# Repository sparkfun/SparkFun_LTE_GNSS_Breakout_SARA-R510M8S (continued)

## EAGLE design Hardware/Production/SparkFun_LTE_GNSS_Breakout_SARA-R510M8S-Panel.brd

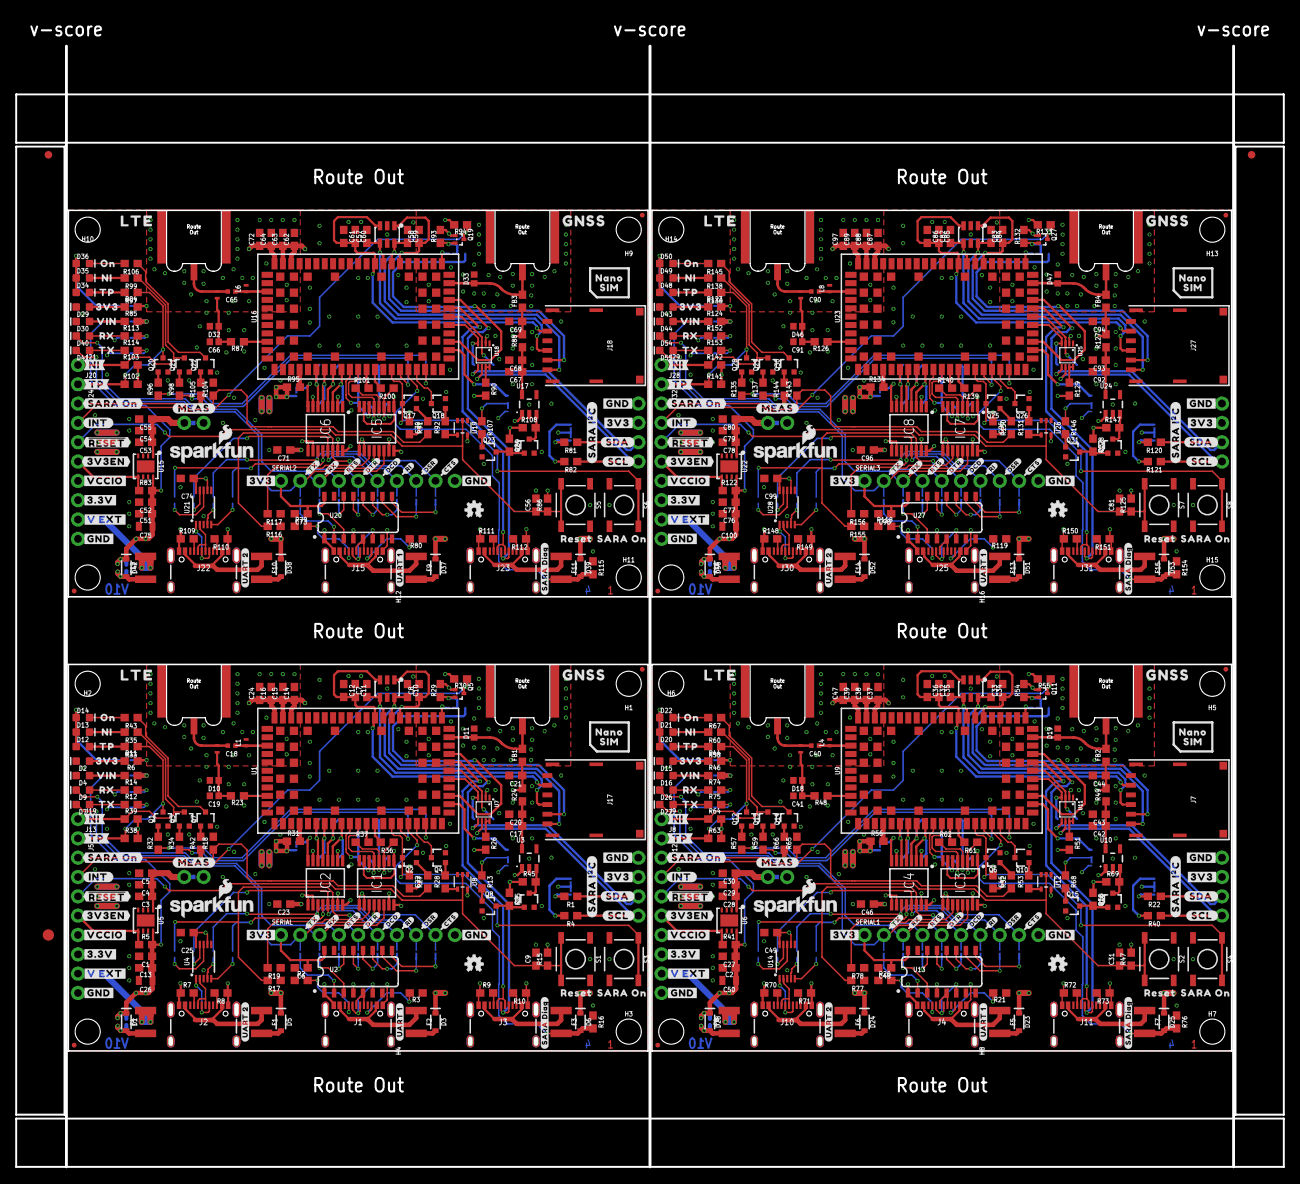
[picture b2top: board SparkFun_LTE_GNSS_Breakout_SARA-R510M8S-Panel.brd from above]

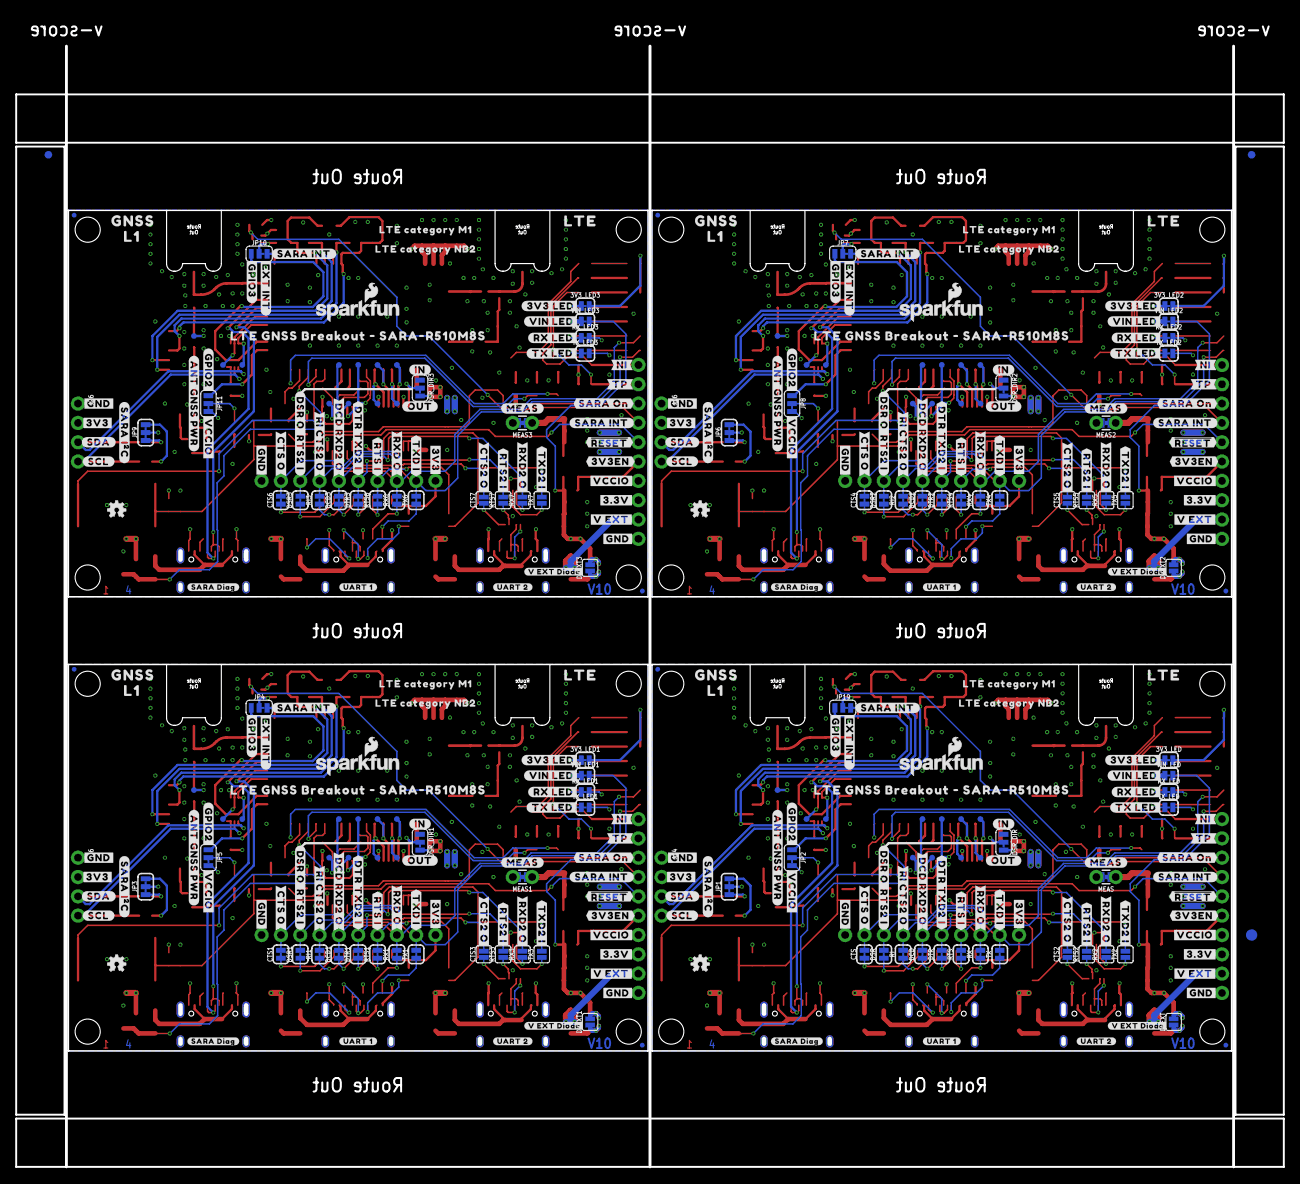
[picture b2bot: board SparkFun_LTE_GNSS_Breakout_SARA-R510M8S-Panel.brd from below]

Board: 4 copper layers, 166.6 x 147.3 mm, 1022 parts (363 on the bottom side), 444 nets.

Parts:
3V3_LED, 3V3_LED1, 3V3_LED2, 3V3_LED3: SMT-JUMPER_2_NC_TRACE_SILK
C1, C4, C6, C9, C12, C14, C20, C22, C23, C25, C27, C29, C31, C36, C37, C43, C45, C46, C48, C49, C52, C54, C56, C61, C62, C68, C70, C71, C73, C74, C77, C79, C81, C86, C87, C93, C95, C96, C98, C99: 0.1uF; 0603
C2, C5, C13, C30, C51, C55, C76, C80: 0.22uF; 0603
C3, C28, C53, C78: 4.7uF; 0603
C7, C8, C10, C11, C21, C32, C33, C34, C35, C44, C57, C58, C59, C60, C69, C82, C83, C84, C85, C94: 47pF; 0603
C15, C38, C63, C88: 68pF; 0603
C16, C39, C64, C89: 10uF; 0603
C17, C42, C67, C92: 1.0uF; 0603
C18, C40, C65, C90: 33pF; 0402-TIGHT
C19, C41, C66, C91: 27pF; 0402
C24, C47, C72, C97: 15pF; 0603
C26, C50, C75, C100: 10uF; 0805
CTS, CTS1, CTS4, CTS6: JUMPER-SMT_2_NC_TRACE_SILK; SMT-JUMPER_2_NC_TRACE_SILK
CTS2, CTS3, CTS5, CTS7: JUMPER-SMT_2_NO_SILK; SMT-JUMPER_2_NO_SILK
D1, D3, D5, D6, D23, D24, D25, D28, D37, D38, D39, D42, D51, D52, D53, D56: 3A/10V/280mV; SOD-323
D2, D15, D29, D43: RED; LED-0603
D4, D9, D16, D26, D30, D40, D44, D54: Yellow; LED-0603
D7, D12, D20, D27, D34, D41, D48, D55: GREEN; LED-0603
D8, D17, D31, D45: DT1042-04SO-7; SOT23-6L
D10, D11, D18, D19, D32, D33, D46, D47: PESD0402; 0402
D13, D21, D35, D49: BLUE; LED-0603
D14, D22, D36, D50: WHITE; LED-0603
DCD, DCD1, DCD2, DCD3: JUMPER-SMT_2_NC_TRACE_SILK; SMT-JUMPER_2_NC_TRACE_SILK
DSR, DSR1, DSR2, DSR3: JUMPER-SMT_2_NC_TRACE_SILK; SMT-JUMPER_2_NC_TRACE_SILK
DSR_DIR, DSR_DIR1, DSR_DIR2, DSR_DIR3: JUMPER-SMT_3_1-NC_TRACE_SILK; SMT-JUMPER_3_1-NC_TRACE_SILK
DTR, DTR1, DTR2, DTR3: JUMPER-SMT_2_NC_TRACE_SILK; SMT-JUMPER_2_NC_TRACE_SILK
DVEXT, DVEXT1, DVEXT2, DVEXT3: JUMPER-SMT_2_NO_SILK; SMT-JUMPER_2_NO_SILK
E1, E2, E3, E4, E5, E6, E7, E8: ANTENNA-SMA-GROUNDEDEDGE_SMA_SMD; SMA-EDGE-SMD
E$1, E$2, E$3, E$4: FIDUCIAL-1X2
E$5, E$6: FIDUCIAL-1.5X3
F1, F2, F3, F4, F5, F6, F7, F8, F9, F10, F11, F12, F13, F14, F15, F16: 6V/2A; 1210
FB1, FB2, FB3, FB4: 30Ω/1.8A; 0603
FD1, FD2, FD3, FD4, FD5, FD6, FD7, FD8, FD9, FD10, FD11, FD12, FD13, FD14, FD15, FD16: FIDUCIALUFIDUCIAL; FIDUCIAL-MICRO
H1, H2, H3, H4, H5, H6, H7, H8, H9, H10, H11, H12, H13, H14, H15, H16: STAND-OFF
IC1, IC2, IC3, IC4, IC5, IC6, IC7, IC8: SN74AVC4T774PW; SOP65P640X120-16N
J1, J2, J3, J4, J10, J11, J15, J22, J23, J25, J30, J31: USB-C-16P_4LAYER-PADS
J5, J12, J24, J32: 1X08_NO_SILK
J6, J14, J16, J26: 1X04_NO_SILK
J7, J17, J18, J27: NANO_SIM; NANO_SIM_WURTH_693043020611
J8, J13, J20, J28: TP; 1X01_NO_SILK
J9, J19, J21, J29: NI; 1X01_NO_SILK
JP1, JP3, JP6, JP9: SMT-JUMPER_3_2-NC_TRACE_SILK
JP2, JP4, JP5, JP7, JP8, JP10, JP11, JP19: JUMPER-SMT_3_1-NC_TRACE_SILK; SMT-JUMPER_3_1-NC_TRACE_SILK
L1, L4, L6, L8: DNP; 0402_COILCRAFT
L2, L3, L5, L7: 68nH; 0402_COILCRAFT
LOGO1, LOGO4, LOGO5, LOGO7, LOGO9, LOGO11, LOGO13, LOGO15: SFE_LOGO_NAME_FLAME.1_INCH; SFE_LOGO_NAME_FLAME_.1
LOGO2, LOGO3, LOGO6, LOGO8, LOGO10, LOGO12, LOGO14, LOGO16: OSHW-LOGOMINI; OSHW-LOGO-MINI
MEAS, MEAS1, MEAS2, MEAS3: COMBO-JUMPER_2_NC_TRACE
Q1, Q2, Q3, Q4, Q6, Q7, Q8, Q9, Q10, Q12, Q13, Q14, Q15, Q16, Q17, Q18, Q20, Q21, Q22, Q23, Q24, Q25, Q26, Q28, Q29, Q30, Q31, Q32: 310mA/60V/1.6Ω; SOT323
Q5, Q11, Q19, Q27: 20V/0.2A/8MHz/1.2Ω/1Vth; SOT-416FL
R1, R4, R22, R29, R30, R40, R54, R55, R81, R82, R93, R94, R120, R121, R132, R133: 2.2k; 0603
R2, R3, R7, R8, R9, R10, R16, R20, R21, R70, R71, R72, R73, R76, R79, R80, R109, R110, R111, R112, R115, R118, R119, R148, R149, R150, R151, R154: 5.1k; 0603
R5, R15, R17, R18, R19, R25, R38, R39, R41, R45, R47, R50, R63, R64, R65, R69, R77, R78, R83, R86, R89, R102, R103, R104, R108, R116, R117, R122, R125, R128, R141, R142, R143, R147, R155, R156: 100k; 0603
R6, R12, R14, R46, R74, R75, R85, R113, R114, R124, R152, R153: 4.7k; 0603
R11, R13, R27, R28, R32, R34, R42, R43, R44, R52, R53, R57, R59, R66, R67, R68, R84, R91, R92, R96, R98, R105, R106, R107, R123, R130, R131, R135, R137, R144, R145, R146: 1k; 0603
R23, R48, R87, R126: 10k; 0603
R24, R49, R88, R127: 10; 0603
R26, R51, R90, R129: 200k; 0603
R31, R36, R37, R56, R61, R62, R95, R100, R101, R134, R139, R140: 0; 0603
R33, R58, R97, R136: 100; 0603
R35, R60, R99, R138: 470; 0603
RI, RI1, RI2, RI3: JUMPER-SMT_2_NC_TRACE_SILK; SMT-JUMPER_2_NC_TRACE_SILK
RTS, RTS1, RTS4, RTS6: JUMPER-SMT_2_NC_TRACE_SILK; SMT-JUMPER_2_NC_TRACE_SILK
RTS2, RTS3, RTS5, RTS7: JUMPER-SMT_2_NO_SILK; SMT-JUMPER_2_NO_SILK
RX, RX1, RX4, RX6: JUMPER-SMT_2_NC_TRACE_SILK; SMT-JUMPER_2_NC_TRACE_SILK
RX2, RX3, RX5, RX7: JUMPER-SMT_2_NO_SILK; SMT-JUMPER_2_NO_SILK
RX_LED, RX_LED1, RX_LED2, RX_LED3: SMT-JUMPER_2_NC_TRACE_SILK
S1, S2, S5, S7: RESET; TACTILE_SWITCH_SMD_5.2MM
S3, S4, S6, S8: SARA_PWR; TACTILE_SWITCH_SMD_5.2MM
SERIAL, SERIAL1, SERIAL2, SERIAL3: 1X10_NO_SILK
TP1, TP2, TP3, TP4, TP5, TP6, TP7, TP8, TP9, TP10, TP11, TP12, TP13, TP14, TP15, TP16, TP17, TP18, TP19, TP20, TP21, TP22, TP23, TP24, TP25, TP26, TP27, TP28, TP29, TP30, TP31, TP32, TP33, TP34, TP35, TP36, TP37, TP38, TP39, TP40, TP41, TP42, TP43, TP44: TEST-POINT3; PAD.03X.03
TX, TX1, TX4, TX6: JUMPER-SMT_2_NC_TRACE_SILK; SMT-JUMPER_2_NC_TRACE_SILK
TX2, TX3, TX5, TX7: JUMPER-SMT_2_NO_SILK; SMT-JUMPER_2_NO_SILK
TX_LED, TX_LED1, TX_LED2, TX_LED3: SMT-JUMPER_2_NC_TRACE_SILK
U1, U9, U16, U23: SARA-R510M8S; SARA-LGA
U2, U13, U20, U27: CH340C; SO016
U3, U10, U17, U24: 3.3V; SOT23-5
U4, U14, U21, U28: CH340E_MSOP10; MSOP10
U5, U6, U15, U22: AP7361C-33FGE; UDFN-8
U7, U11, U18, U25: PCA9306; VSSOP_8PIN
U8, U12, U19, U26: 74HC1G04; SOT353
U$1, U$2, U$3, U$11, U$93, U$94, U$134, U$135, U$195, U$196, U$228, U$229, U$289, U$290, U$322, U$323: #3V3#1
U$4, U$167, U$261, U$355: #TX_LED#0
U$5, U$23, U$120, U$121, U$216, U$217, U$310, U$311: #SARA_I�C#0
U$6, U$7, U$136, U$137, U$230, U$231, U$324, U$325: #V_EXT#0
U$8, U$9, U$138, U$139, U$232, U$233, U$326, U$327: #3V3EN#0
U$10, U$13, U$140, U$141, U$234, U$235, U$328, U$329: ##RESET##0
U$12, U$22, U$95, U$96, U$197, U$198, U$291, U$292: #GND#0
U$14, U$142, U$236, U$330: #INT#0
U$15, U$71, U$182, U$183, U$276, U$277, U$370, U$371: #SARA_INT#0
U$16, U$17, U$143, U$144, U$237, U$238, U$331, U$332: #SARA_ON#0
U$18, U$145, U$239, U$333: RX0
U$19, U$87, U$92, U$115, U$194, U$213, U$288, U$307: #MEAS#2
U$20, U$168, U$262, U$356: #RX_LED#0
U$21, U$146, U$240, U$334: TX0
U$24, U$147, U$241, U$335: #TX#0
U$25, U$148, U$242, U$336: #RX#0
U$26, U$27, U$97, U$98, U$199, U$200, U$293, U$294: #SCL#3
U$28, U$149, U$243, U$337: #RTS#0
U$29, U$150, U$244, U$338: #DTR#0
U$30, U$37, U$102, U$103, U$201, U$202, U$295, U$296: #SDA#2
U$31, U$151, U$245, U$339: #DCD#0
U$32, U$152, U$246, U$340: #RI#0
U$33, U$153, U$247, U$341: #DSR#0
U$34, U$154, U$248, U$342: #CTS#0
U$35, U$155, U$249, U$343: #RXD_O#0
U$36, U$84, U$191, U$285: 3V37
U$38, U$156, U$250, U$344: #TXD_I#0
U$39, U$157, U$251, U$345: #CTS_O#0
U$40, U$158, U$252, U$346: #RTS_I#0
U$41, U$159, U$253, U$347: #DTR_TXD2_I#0
U$42, U$188, U$282, U$376: L10
U$43, U$160, U$254, U$348: #DCD_RXD2_O#0
U$44, U$161, U$255, U$349: #RXD2_O#0
U$45, U$85, U$192, U$286: RESET6
U$46, U$86, U$193, U$287: VIN8
U$47, U$162, U$256, U$350: #RI_CTS2_O#0
U$48, U$163, U$257, U$351: #CTS2_O#0
U$49, U$171, U$265, U$359: #DSR_O__RTS2_I#0
U$50, U$164, U$258, U$352: #RTS2_I#0
U$51, U$172, U$266, U$360: #V_EXT_DIODE#0
U$52, U$165, U$259, U$353: #OUT#0
U$53, U$166, U$260, U$354: #IN#0
U$54, U$169, U$263, U$357: #VIN_LED#0
U$55, U$56, U$77, U$78, U$81, U$82, U$104, U$105, U$189, U$190, U$203, U$204, U$283, U$284, U$297, U$298: #GND#4
U$57, U$58, U$106, U$107, U$205, U$206, U$299, U$300: #TP#0
U$59, U$60, U$108, U$109, U$207, U$208, U$301, U$302: #NI#0
U$61, U$170, U$264, U$358: #3V3_LED#0
U$62, U$63, U$173, U$174, U$267, U$268, U$361, U$362: #UART_2#0
U$64, U$65, U$175, U$176, U$269, U$270, U$363, U$364: #UART_1#0
U$66, U$67, U$177, U$178, U$271, U$272, U$365, U$366: #SARA_DIAG#0
U$68, U$80, U$83, U$112, U$114, U$179, U$211, U$212, U$273, U$305, U$306, U$367: #VCCIO#0
U$69, U$180, U$274, U$368: #GPIO2#0
U$70, U$181, U$275, U$369: #ANT_GNSS_PWR#0
U$72, U$187, U$281, U$375: #TXD2_I#0
U$73, U$184, U$278, U$372: LTE_CATEGORY_M10
U$74, U$185, U$279, U$373: LTE_CATEGORY_NB20
U$75, U$186, U$280, U$374: LTE_GNSS_BREAKOUT_#_SARA#R510M8S0
U$76, U$79, U$110, U$111, U$209, U$210, U$303, U$304: #3#3V#0
U$88, U$89, U$122, U$123, U$218, U$219, U$312, U$313: LTE0
U$90, U$116, U$214, U$308: NI0
U$91, U$117, U$215, U$309: TP0
U$99, U$100, U$124, U$125, U$220, U$221, U$314, U$315: GNSS0
U$101, U$127, U$223, U$317: ON0
U$113, U$126, U$222, U$316: SARA_ON0
U$118, U$132, U$226, U$320: #EXT_INT#0
U$119, U$133, U$227, U$321: #GPIO3#0
U$128, U$130, U$224, U$318: NANO0
U$129, U$131, U$225, U$319: SIM0
VIN_LED, VIN_LED1, VIN_LED2, VIN_LED3: SMT-JUMPER_2_NC_TRACE_SILK

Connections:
3.3V: 3V3_LED.2, C6.1, C14.1, C15.1, C16.1, C24.1, C25.1, D12.A, D13.A, D14.A, IC1.15, IC2.15, J5.6, J14.2, JP1.2, MEAS.2, MEAS.4, R15.2, R25.1, R26.2, R30.2, R38.2, R39.2, R45.1, RX_LED.2, SERIAL.1, TX_LED.2, U1.51, U1.52, U1.53, U2.4, U2.16, U4.7, U4.10, U8.5
3.3V1: 3V3_LED1.2, C37.1, C38.1, C39.1, C47.1, C48.1, C49.1, D20.A, D21.A, D22.A, IC3.15, IC4.15, J6.2, J12.6, JP3.2, MEAS1.2, MEAS1.4, R47.2, R50.1, R51.2, R55.2, R63.2, R64.2, R69.1, RX_LED1.2, SERIAL1.1, TX_LED1.2, U9.51, U9.52, U9.53, U12.5, U13.4, U13.16, U14.7, U14.10
3.3V2: 3V3_LED2.2, C62.1, C63.1, C64.1, C72.1, C73.1, C74.1, D34.A, D35.A, D36.A, IC5.15, IC6.15, J16.2, J24.6, JP6.2, MEAS2.2, MEAS2.4, R86.2, R89.1, R90.2, R94.2, R102.2, R103.2, R108.1, RX_LED2.2, SERIAL2.1, TX_LED2.2, U16.51, U16.52, U16.53, U19.5, U20.4, U20.16, U21.7, U21.10
3.3V3: 3V3_LED3.2, C87.1, C88.1, C89.1, C97.1, C98.1, C99.1, D48.A, D49.A, D50.A, IC7.15, IC8.15, J26.2, J32.6, JP9.2, MEAS3.2, MEAS3.4, R125.2, R128.1, R129.2, R133.2, R141.2, R142.2, R147.1, RX_LED3.2, SERIAL3.1, TX_LED3.2, U23.51, U23.52, U23.53, U26.5, U27.4, U27.16, U28.7, U28.10
3.3V_EN: J5.4, R5.1, U5.5
3.3V_EN1: J12.4, R41.1, U6.5
3.3V_EN2: J24.4, R83.1, U15.5
3.3V_EN3: J32.4, R122.1, U22.5
!RESET!: C9.1, J5.3, R15.1, S1.3, S1.4, U8.2
!RESET!1: C31.1, J12.3, R47.1, S2.3, S2.4, U12.2
!RESET!2: C56.1, J24.3, R86.1, S5.3, S5.4, U19.2
!RESET!3: C81.1, J32.3, R125.1, S7.3, S7.4, U26.2
ANT_REG_EN: Q9.3, R45.2, U3.3
ANT_REG_EN1: Q16.3, R69.2, U10.3
ANT_REG_EN2: Q24.3, R108.2, U17.3
ANT_REG_EN3: Q32.3, R147.2, U24.3
CTS: CTS.2, IC1.12, SERIAL.9
CTS1: CTS1.2, IC3.12, SERIAL1.9
CTS2: CTS4.2, IC5.12, SERIAL2.9
CTS3: CTS6.2, IC7.12, SERIAL3.9
DCD: DCD.2, IC2.13, RX2.2, SERIAL.6
DCD1: DCD1.2, IC4.13, RX3.2, SERIAL1.6
DCD2: DCD2.2, IC6.13, RX5.2, SERIAL2.6
DCD3: DCD3.2, IC8.13, RX7.2, SERIAL3.6
DSR: DSR.2, IC2.11, RTS2.2, SERIAL.8
DSR1: DSR1.2, IC4.11, RTS3.2, SERIAL1.8
DSR2: DSR2.2, IC6.11, RTS5.2, SERIAL2.8
DSR3: DSR3.2, IC8.11, RTS7.2, SERIAL3.8
DTR: DTR.2, IC2.14, R17.2, SERIAL.5, TX2.2
DTR1: DTR1.2, IC4.14, R77.2, SERIAL1.5, TX3.2
DTR2: DTR2.2, IC6.14, R116.2, SERIAL2.5, TX5.2
DTR3: DTR3.2, IC8.14, R155.2, SERIAL3.5, TX7.2
GND: C1.2, C3.2, C4.2, C5.2, C6.2, C7.2, C8.2, C9.2, C10.1, C11.1, C12.1, C13.2, C14.2, C15.2, C16.2, C17.2, C19.2, C20.2, C21.2, C22.2, C23.2, C24.2, C25.2, C26.2, D2.C, D4.C, D8.2, D8.5, D10.2, D11.2, DSR_DIR.1, E3.GND@0, E3.GND@1, E4.GND@0, E4.GND@1, IC1.2, IC1.8, IC1.9, IC1.10, IC2.1, IC2.9, IC2.10, J1.GND, J1.GND2, J2.GND, J2.GND2, J3.GND, J3.GND2, J5.8, J14.1, J17.C5, L1.P$2, Q1.2, Q2.2, Q3.2, Q4.2, Q7.2, Q8.2, Q9.2, R2.1, R3.1, R7.1, R8.1, R9.1, R10.1, R16.1, R17.1, R18.2, R19.1, S1.1, S1.2, S3.3, S3.4, SERIAL.10, U1.1, U1.3, U1.5, U1.14, U1.20, U1.21, U1.22, U1.30, U1.32, U1.43, U1.50, U1.54, U1.55, U1.57, U1.58, U1.59, U1.60, U1.61, U1.63, U1.64, U1.65, U1.66, U1.67, U1.68, U1.69, U1.70, U1.71, U1.72, U1.73, U1.74, U1.75, U1.76, U1.77, U1.78, U1.79, U1.80, U1.81, U1.82, U1.83, U1.84, U1.85, U1.86, U1.87, U1.88, U1.89, U1.90, U1.91, U1.92, U1.93, U1.94, U1.95, U1.96, U2.1, U3.2, U4.3, U5.4, U5.EP, U7.P1, U8.3
GND1: C2.2, C27.2, C28.2, C29.2, C30.2, C31.2, C32.2, C33.2, C34.1, C35.1, C36.1, C37.2, C38.2, C39.2, C41.2, C42.2, C43.2, C44.2, C45.2, C46.2, C47.2, C48.2, C49.2, C50.2, D15.C, D16.C, D17.2, D17.5, D18.2, D19.2, DSR_DIR1.1, E1.GND@0, E1.GND@1, E2.GND@0, E2.GND@1, IC3.2, IC3.8, IC3.9, IC3.10, IC4.1, IC4.9, IC4.10, J4.GND, J4.GND2, J6.1, J7.C5, J10.GND, J10.GND2, J11.GND, J11.GND2, J12.8, L4.P$2, Q6.2, Q10.2, Q12.2, Q13.2, Q14.2, Q15.2, Q16.2, R20.1, R21.1, R65.2, R70.1, R71.1, R72.1, R73.1, R76.1, R77.1, R78.1, S2.1, S2.2, S4.3, S4.4, SERIAL1.10, U6.4, U6.EP, U9.1, U9.3, U9.5, U9.14, U9.20, U9.21, U9.22, U9.30, U9.32, U9.43, U9.50, U9.54, U9.55, U9.57, U9.58, U9.59, U9.60, U9.61, U9.63, U9.64, U9.65, U9.66, U9.67, U9.68, U9.69, U9.70, U9.71, U9.72, U9.73, U9.74, U9.75, U9.76, U9.77, U9.78, U9.79, U9.80, U9.81, U9.82, U9.83, U9.84, U9.85, U9.86, U9.87, U9.88, U9.89, U9.90, U9.91, U9.92, U9.93, U9.94, U9.95, U9.96, U10.2, U11.P1, U12.3, U13.1, U14.3
GND2: C51.2, C52.2, C53.2, C54.2, C55.2, C56.2, C57.2, C58.2, C59.1, C60.1, C61.1, C62.2, C63.2, C64.2, C66.2, C67.2, C68.2, C69.2, C70.2, C71.2, C72.2, C73.2, C74.2, C75.2, D29.C, D30.C, D31.2, D31.5, D32.2, D33.2, DSR_DIR2.1, E5.GND@0, E5.GND@1, E6.GND@0, E6.GND@1, IC5.2, IC5.8, IC5.9, IC5.10, IC6.1, IC6.9, IC6.10, J15.GND, J15.GND2, J16.1, J18.C5, J22.GND, J22.GND2, J23.GND, J23.GND2, J24.8, L6.P$2, Q17.2, Q18.2, Q20.2, Q21.2, Q22.2, Q23.2, Q24.2, R79.1, R80.1, R104.2, R109.1, R110.1, R111.1, R112.1, R115.1, R116.1, R117.1, S5.1, S5.2, S6.3, S6.4, SERIAL2.10, U15.4, U15.EP, U16.1, U16.3, U16.5, U16.14, U16.20, U16.21, U16.22, U16.30, U16.32, U16.43, U16.50, U16.54, U16.55, U16.57, U16.58, U16.59, U16.60, U16.61, U16.63, U16.64, U16.65, U16.66, U16.67, U16.68, U16.69, U16.70, U16.71, U16.72, U16.73, U16.74, U16.75, U16.76, U16.77, U16.78, U16.79, U16.80, U16.81, U16.82, U16.83, U16.84, U16.85, U16.86, U16.87, U16.88, U16.89, U16.90, U16.91, U16.92, U16.93, U16.94, U16.95, U16.96, U17.2, U18.P1, U19.3, U20.1, U21.3
GND3: C76.2, C77.2, C78.2, C79.2, C80.2, C81.2, C82.2, C83.2, C84.1, C85.1, C86.1, C87.2, C88.2, C89.2, C91.2, C92.2, C93.2, C94.2, C95.2, C96.2, C97.2, C98.2, C99.2, C100.2, D43.C, D44.C, D45.2, D45.5, D46.2, D47.2, DSR_DIR3.1, E7.GND@0, E7.GND@1, E8.GND@0, E8.GND@1, IC7.2, IC7.8, IC7.9, IC7.10, IC8.1, IC8.9, IC8.10, J25.GND, J25.GND2, J26.1, J27.C5, J30.GND, J30.GND2, J31.GND, J31.GND2, J32.8, L8.P$2, Q25.2, Q26.2, Q28.2, Q29.2, Q30.2, Q31.2, Q32.2, R118.1, R119.1, R143.2, R148.1, R149.1, R150.1, R151.1, R154.1, R155.1, R156.1, S7.1, S7.2, S8.3, S8.4, SERIAL3.10, U22.4, U22.EP, U23.1, U23.3, U23.5, U23.14, U23.20, U23.21, U23.22, U23.30, U23.32, U23.43, U23.50, U23.54, U23.55, U23.57, U23.58, U23.59, U23.60, U23.61, U23.63, U23.64, U23.65, U23.66, U23.67, U23.68, U23.69, U23.70, U23.71, U23.72, U23.73, U23.74, U23.75, U23.76, U23.77, U23.78, U23.79, U23.80, U23.81, U23.82, U23.83, U23.84, U23.85, U23.86, U23.87, U23.88, U23.89, U23.90, U23.91, U23.92, U23.93, U23.94, U23.95, U23.96, U24.2, U25.P1, U26.3, U27.1, U28.3
unnamed: R6.2, VIN_LED.1
unnamed: JP1.3, R4.2
unnamed: JP1.1, R1.2
unnamed: D3.A, F2.2
unnamed: J2.A5, R7.2
unnamed: 3V3_LED.1, R11.2
unnamed: D2.A, R11.1
unnamed: D4.A, R6.1
unnamed: J2.B5, R8.2
unnamed: J1.A5, R2.2
unnamed: J1.B5, R3.2
unnamed: D5.A, F1.2
unnamed: F1.1, J2.VBUS1, J2.VBUS2
unnamed: J3.A5, R9.2
unnamed: C18.2, E3.SIG, L2.P$2
unnamed: C19.1, D10.1, L2.P$1, R23.2
unnamed: J3.B5, R10.2
unnamed: F3.1, J3.VBUS1, J3.VBUS2
unnamed: F2.1, J1.VBUS1, J1.VBUS2
unnamed: TX.1, U2.2
unnamed: RX.1, U2.3
unnamed: R26.1, U7.P7, U7.P8
unnamed: DSR_DIR.2, IC2.8
unnamed: C17.1, C20.1, R24.1, U3.5
unnamed: C21.1, FB1.1, R24.2, TP22.P$1
unnamed: Q2.1, R27.2
unnamed: Q4.1, R28.2
unnamed: R28.1, U8.4
unnamed: RTS.1, U2.14
unnamed: DTR.1, U2.13
unnamed: R31.2, U1.4
unnamed: Q1.1, R32.2
unnamed: J13.1, Q1.3, R33.1, R38.1
unnamed: D12.C, R33.2
unnamed: Q3.1, R34.2
unnamed: J19.1, Q3.3, R35.1, R39.1
unnamed: D13.C, R35.2
unnamed: R36.2, U1.13
unnamed: R37.2, U1.12
unnamed: Q8.1, R13.2
unnamed: DCD.1, U2.12
unnamed: Q8.3, Q9.1, R25.2
unnamed: JP19.2, Q5.2, R29.1
unnamed: RI.1, U2.11
unnamed: DSR.1, U2.10
unnamed: CTS.1, U2.9
unnamed: Q7.1, R42.2
unnamed: TX2.1, U4.8
unnamed: D14.C, R43.2
unnamed: RX2.1, U4.9
unnamed: RTS2.1, U4.4
unnamed: CTS2.1, U4.5
unnamed: R12.2, TX_LED.1
unnamed: D7.A, R12.1
unnamed: R14.2, RX_LED.1
unnamed: D9.A, R14.1
unnamed: D1.A, DVEXT.1, F4.1
unnamed: JP2.2, R13.1
unnamed: J4.A5, R20.2
unnamed: J4.B5, R21.2
unnamed: JP3.3, R40.2
unnamed: JP3.1, R22.2
unnamed: 3V3_LED1.1, R44.2
unnamed: D15.A, R44.1
unnamed: R46.2, VIN_LED1.1
unnamed: D16.A, R46.1
unnamed: C40.2, E1.SIG, L3.P$2
unnamed: C41.1, D18.1, L3.P$1, R48.2
unnamed: C42.1, C43.1, R49.1, U10.5
unnamed: C44.1, FB2.1, R49.2, TP21.P$1
unnamed: R51.1, U11.P7, U11.P8
unnamed: Q6.1, R52.2
unnamed: Q10.1, R53.2
unnamed: R53.1, U12.4
unnamed: R56.2, U9.4
unnamed: Q12.1, R57.2
unnamed: J8.1, Q12.3, R58.1, R63.1
unnamed: D20.C, R58.2
unnamed: Q13.1, R59.2
unnamed: J9.1, Q13.3, R60.1, R64.1
unnamed: D21.C, R60.2
unnamed: R61.2, U9.13
unnamed: R62.2, U9.12
unnamed: Q14.1, R66.2
unnamed: D22.C, R67.2
unnamed: DSR_DIR1.2, IC4.8
unnamed: Q15.1, R68.2
unnamed: Q15.3, Q16.1, R50.2
unnamed: JP4.2, Q11.2, R54.1
unnamed: D23.A, F5.2
unnamed: J10.A5, R70.2
unnamed: J10.B5, R71.2
unnamed: D24.A, F6.2
unnamed: F6.1, J10.VBUS1, J10.VBUS2
unnamed: J11.A5, R72.2
unnamed: J11.B5, R73.2
unnamed: F5.1, J4.VBUS1, J4.VBUS2
unnamed: TX1.1, U13.2
unnamed: RX1.1, U13.3
unnamed: RTS1.1, U13.14
unnamed: DTR1.1, U13.13
unnamed: DCD1.1, U13.12
unnamed: RI1.1, U13.11
unnamed: DSR1.1, U13.10
unnamed: CTS1.1, U13.9
unnamed: TX3.1, U14.8
unnamed: RX3.1, U14.9
unnamed: RTS3.1, U14.4
unnamed: CTS3.1, U14.5
unnamed: F7.1, J11.VBUS1, J11.VBUS2
unnamed: R74.2, RX_LED1.1
unnamed: D26.A, R74.1
unnamed: R75.2, TX_LED1.1
unnamed: D27.A, R75.1
unnamed: D28.A, DVEXT1.1, F8.1
unnamed: JP5.2, R68.1
unnamed: J15.A5, R79.2
unnamed: J15.B5, R80.2
unnamed: JP6.3, R82.2
unnamed: JP6.1, R81.2
unnamed: 3V3_LED2.1, R84.2
unnamed: D29.A, R84.1
unnamed: R85.2, VIN_LED2.1
unnamed: D30.A, R85.1
unnamed: C65.2, E5.SIG, L5.P$2
unnamed: C66.1, D32.1, L5.P$1, R87.2
unnamed: C67.1, C68.1, R88.1, U17.5
unnamed: C69.1, FB3.1, R88.2, TP33.P$1
unnamed: R90.1, U18.P7, U18.P8
unnamed: Q17.1, R91.2
unnamed: Q18.1, R92.2
unnamed: R92.1, U19.4
unnamed: R95.2, U16.4
unnamed: Q20.1, R96.2
unnamed: J20.1, Q20.3, R97.1, R102.1
unnamed: D34.C, R97.2
unnamed: Q21.1, R98.2
unnamed: J21.1, Q21.3, R99.1, R103.1
unnamed: D35.C, R99.2
unnamed: R100.2, U16.13
unnamed: R101.2, U16.12
unnamed: Q22.1, R105.2
unnamed: D36.C, R106.2
unnamed: DSR_DIR2.2, IC6.8
unnamed: Q23.1, R107.2
unnamed: Q23.3, Q24.1, R89.2
unnamed: JP7.2, Q19.2, R93.1
unnamed: D37.A, F9.2
unnamed: J22.A5, R109.2
unnamed: J22.B5, R110.2
unnamed: D38.A, F10.2
unnamed: F10.1, J22.VBUS1, J22.VBUS2
unnamed: J23.A5, R111.2
unnamed: J23.B5, R112.2
unnamed: F9.1, J15.VBUS1, J15.VBUS2
unnamed: TX4.1, U20.2
unnamed: RX4.1, U20.3
unnamed: RTS4.1, U20.14
unnamed: DTR2.1, U20.13
unnamed: DCD2.1, U20.12
unnamed: RI2.1, U20.11
unnamed: DSR2.1, U20.10
unnamed: CTS4.1, U20.9
unnamed: TX5.1, U21.8
unnamed: RX5.1, U21.9
unnamed: RTS5.1, U21.4
unnamed: CTS5.1, U21.5
unnamed: F11.1, J23.VBUS1, J23.VBUS2
unnamed: R113.2, RX_LED2.1
unnamed: D40.A, R113.1
unnamed: R114.2, TX_LED2.1
unnamed: D41.A, R114.1
unnamed: D42.A, DVEXT2.1, F12.1
unnamed: JP8.2, R107.1
unnamed: J25.A5, R118.2
unnamed: J25.B5, R119.2
unnamed: JP9.3, R121.2
unnamed: JP9.1, R120.2
unnamed: 3V3_LED3.1, R123.2
unnamed: D43.A, R123.1
unnamed: R124.2, VIN_LED3.1
unnamed: D44.A, R124.1
unnamed: C90.2, E7.SIG, L7.P$2
unnamed: C91.1, D46.1, L7.P$1, R126.2
unnamed: C92.1, C93.1, R127.1, U24.5
unnamed: C94.1, FB4.1, R127.2, TP44.P$1
unnamed: R129.1, U25.P7, U25.P8
unnamed: Q25.1, R130.2
unnamed: Q26.1, R131.2
unnamed: R131.1, U26.4
unnamed: R134.2, U23.4
unnamed: Q28.1, R135.2
unnamed: J28.1, Q28.3, R136.1, R141.1
unnamed: D48.C, R136.2
unnamed: Q29.1, R137.2
unnamed: J29.1, Q29.3, R138.1, R142.1
unnamed: D49.C, R138.2
unnamed: R139.2, U23.13
unnamed: R140.2, U23.12
unnamed: Q30.1, R144.2
unnamed: D50.C, R145.2
unnamed: DSR_DIR3.2, IC8.8
unnamed: Q31.1, R146.2
unnamed: Q31.3, Q32.1, R128.2
unnamed: JP10.2, Q27.2, R132.1
unnamed: D51.A, F13.2
unnamed: J30.A5, R148.2
unnamed: J30.B5, R149.2
unnamed: D52.A, F14.2
unnamed: F14.1, J30.VBUS1, J30.VBUS2
unnamed: J31.A5, R150.2
unnamed: J31.B5, R151.2
unnamed: F13.1, J25.VBUS1, J25.VBUS2
unnamed: TX6.1, U27.2
unnamed: RX6.1, U27.3
unnamed: RTS6.1, U27.14
unnamed: DTR3.1, U27.13
unnamed: DCD3.1, U27.12
unnamed: RI3.1, U27.11
unnamed: DSR3.1, U27.10
unnamed: CTS6.1, U27.9
unnamed: TX7.1, U28.8
unnamed: RX7.1, U28.9
unnamed: RTS7.1, U28.4
unnamed: CTS7.1, U28.5
unnamed: F15.1, J31.VBUS1, J31.VBUS2
unnamed: R152.2, RX_LED3.1
unnamed: D54.A, R152.1
unnamed: R153.2, TX_LED3.1
unnamed: D55.A, R153.1
unnamed: D56.A, DVEXT3.1, F16.1
unnamed: JP11.2, R146.1
RI: CTS2.2, IC2.12, RI.2, SERIAL.7
RI1: CTS3.2, IC4.12, RI1.2, SERIAL1.7
RI2: CTS5.2, IC6.12, RI2.2, SERIAL2.7
RI3: CTS7.2, IC8.12, RI3.2, SERIAL3.7
RTS: IC1.11, R19.2, RTS.2, SERIAL.4
RTS1: IC3.11, R78.2, RTS1.2, SERIAL1.4
RTS2: IC5.11, R117.2, RTS4.2, SERIAL2.4
RTS3: IC7.11, R156.2, RTS6.2, SERIAL3.4
RX: D9.C, IC1.14, RX.2, SERIAL.3
RX1: D26.C, IC3.14, RX1.2, SERIAL1.3
RX2: D40.C, IC5.14, RX4.2, SERIAL2.3
RX3: D54.C, IC7.14, RX6.2, SERIAL3.3
SARA_!ON!: Q7.3, R43.1
SARA_!ON!1: Q14.3, R67.1
SARA_!ON!2: Q22.3, R106.1
SARA_!ON!3: Q30.3, R145.1
SARA_!RESET!: Q4.3, U1.18
SARA_!RESET!1: Q10.3, U9.18
SARA_!RESET!2: Q18.3, U16.18
SARA_!RESET!3: Q26.3, U23.18
SARA_ANT: C18.1, L1.P$1, U1.56
SARA_ANT1: C40.1, L4.P$1, U9.56
SARA_ANT2: C65.1, L6.P$1, U16.56
SARA_ANT3: C90.1, L8.P$1, U23.56
SARA_ANT_DET: R23.1, U1.62
SARA_ANT_DET1: R48.1, U9.62
SARA_ANT_DET2: R87.1, U16.62
SARA_ANT_DET3: R126.1, U23.62
SARA_ANT_GNSS: D11.1, E4.SIG, FB1.2, U1.31
SARA_ANT_GNSS1: D19.1, E2.SIG, FB2.2, U9.31
SARA_ANT_GNSS2: D33.1, E6.SIG, FB3.2, U16.31
SARA_ANT_GNSS3: D47.1, E8.SIG, FB4.2, U23.31
SARA_CTS_O: IC1.5, TP3.P$1, U1.11
SARA_CTS_O1: IC3.5, TP7.P$1, U9.11
SARA_CTS_O2: IC5.5, TP25.P$1, U16.11
SARA_CTS_O3: IC7.5, TP36.P$1, U23.11
SARA_DCD/RXD2O: IC2.4, TP15.P$1, U1.8
SARA_DCD/RXD2O1: IC4.4, TP18.P$1, U9.8
SARA_DCD/RXD2O2: IC6.4, TP30.P$1, U16.8
SARA_DCD/RXD2O3: IC8.4, TP41.P$1, U23.8
SARA_DSR/RTS2I: IC2.6, TP17.P$1, U1.6
SARA_DSR/RTS2I1: IC4.6, TP20.P$1, U9.6
SARA_DSR/RTS2I2: IC6.6, TP32.P$1, U16.6
SARA_DSR/RTS2I3: IC8.6, TP43.P$1, U23.6
SARA_DTR/TXD2I: IC2.3, TP14.P$1, U1.9
SARA_DTR/TXD2I1: IC4.3, TP13.P$1, U9.9
SARA_DTR/TXD2I2: IC6.3, TP29.P$1, U16.9
SARA_DTR/TXD2I3: IC8.3, TP40.P$1, U23.9
SARA_EXT_INT: JP19.3, U1.33
SARA_EXT_INT1: JP4.3, U9.33
SARA_EXT_INT2: JP7.3, U16.33
SARA_EXT_INT3: JP10.3, U23.33
SARA_GPIO1: JP5.1, U9.23
SARA_GPIO2: JP2.1, U1.23
SARA_GPIO3: JP19.1, U1.24
SARA_GPIO4: JP4.1, U9.24
SARA_GPIO5: JP8.1, U16.23
SARA_GPIO6: JP7.1, U16.24
SARA_GPIO7: JP11.1, U23.23
SARA_GPIO8: JP10.1, U23.24
SARA_INT: J5.2, Q5.3, R30.1
SARA_INT1: J12.2, Q11.3, R55.1
SARA_INT2: J24.2, Q19.3, R94.1
SARA_INT3: J32.2, Q27.3, R133.1
SARA_NI: R34.1, U1.16
SARA_NI1: R59.1, U9.16
SARA_NI2: R98.1, U16.16
SARA_NI3: R137.1, U23.16
SARA_ON: J5.1, R18.1, R27.1
SARA_ON1: J12.1, R52.1, R65.1
SARA_ON2: J24.1, R91.1, R104.1
SARA_ON3: J32.1, R130.1, R143.1
SARA_ON_1.8V: Q2.3, S3.1, S3.2, U1.15
SARA_ON_1.8V1: Q6.3, S4.1, S4.2, U9.15
SARA_ON_1.8V2: Q17.3, S6.1, S6.2, U16.15
SARA_ON_1.8V3: Q25.3, S8.1, S8.2, U23.15
SARA_RI/CTS2O: IC2.5, TP16.P$1, U1.7
SARA_RI/CTS2O1: IC4.5, TP19.P$1, U9.7
SARA_RI/CTS2O2: IC6.5, TP31.P$1, U16.7
SARA_RI/CTS2O3: IC8.5, TP42.P$1, U23.7
SARA_RTS_I: IC1.6, TP4.P$1, U1.10
SARA_RTS_I1: IC3.6, TP8.P$1, U9.10
SARA_RTS_I2: IC5.6, TP26.P$1, U16.10
SARA_RTS_I3: IC7.6, TP37.P$1, U23.10
SARA_RXD_O: IC1.3, R36.1, TP1.P$1
SARA_RXD_O1: IC3.3, R61.1, TP5.P$1
SARA_RXD_O2: IC5.3, R100.1, TP23.P$1
SARA_RXD_O3: IC7.3, R139.1, TP34.P$1
SARA_SCL: J14.4, R4.1, U7.P6
SARA_SCL1: J6.4, R40.1, U11.P6
SARA_SCL2: J16.4, R82.1, U18.P6
SARA_SCL3: J26.4, R121.1, U25.P6
SARA_SCL_1.8V: TP10.P$1, U1.27, U7.P3
SARA_SCL_1.8V1: TP12.P$1, U9.27, U11.P3
SARA_SCL_1.8V2: TP28.P$1, U16.27, U18.P3
SARA_SCL_1.8V3: TP39.P$1, U23.27, U25.P3
SARA_SDA: J14.3, R1.1, U7.P5
SARA_SDA1: J6.3, R22.1, U11.P5
SARA_SDA2: J16.3, R81.1, U18.P5
SARA_SDA3: J26.3, R120.1, U25.P5
SARA_SDA_1.8V: TP9.P$1, U1.26, U7.P4
SARA_SDA_1.8V1: TP11.P$1, U9.26, U11.P4
SARA_SDA_1.8V2: TP27.P$1, U16.26, U18.P4
SARA_SDA_1.8V3: TP38.P$1, U23.26, U25.P4
SARA_TP: R32.1, U1.19
SARA_TP1: R57.1, U9.19
SARA_TP2: R96.1, U16.19
SARA_TP3: R135.1, U23.19
SARA_TXD_I: IC1.4, R37.1, TP2.P$1
SARA_TXD_I1: IC3.4, R62.1, TP6.P$1
SARA_TXD_I2: IC5.4, R101.1, TP24.P$1
SARA_TXD_I3: IC7.4, R140.1, TP35.P$1
SARA_USB_D+: J3.A6, J3.B6, U1.29
SARA_USB_D+1: J11.A6, J11.B6, U9.29
SARA_USB_D+2: J23.A6, J23.B6, U16.29
SARA_USB_D+3: J31.A6, J31.B6, U23.29
SARA_USB_D-: J3.A7, J3.B7, U1.28
SARA_USB_D-1: J11.A7, J11.B7, U9.28
SARA_USB_D-2: J23.A7, J23.B7, U16.28
SARA_USB_D-3: J31.A7, J31.B7, U23.28
SARA_VUSB_DET: D6.A, F3.2, R16.2, U1.17
SARA_VUSB_DET1: D25.A, F7.2, R76.2, U9.17
SARA_VUSB_DET2: D39.A, F11.2, R115.2, U16.17
SARA_VUSB_DET3: D53.A, F15.2, R154.2, U23.17
SIM_CLK: C8.1, D8.1, J17.C3, U1.38
SIM_CLK1: C33.1, D17.1, J7.C3, U9.38
SIM_CLK2: C58.1, D31.1, J18.C3, U16.38
SIM_CLK3: C83.1, D45.1, J27.C3, U23.38
SIM_IO: C10.2, D8.6, J17.C7, U1.39
SIM_IO1: C34.2, D17.6, J7.C7, U9.39
SIM_IO2: C59.2, D31.6, J18.C7, U16.39
SIM_IO3: C84.2, D45.6, J27.C7, U23.39
SIM_RST: C7.1, D8.4, J17.C2, U1.40
SIM_RST1: C32.1, D17.4, J7.C2, U9.40
SIM_RST2: C57.1, D31.4, J18.C2, U16.40
SIM_RST3: C82.1, D45.4, J27.C2, U23.40
TX: D7.C, IC1.13, SERIAL.2, TX.2
TX1: D27.C, IC3.13, SERIAL1.2, TX1.2
TX2: D41.C, IC5.13, SERIAL2.2, TX4.2
TX3: D55.C, IC7.13, SERIAL3.2, TX6.2
USB_2_D+: J2.A6, J2.B6, U4.1
USB_2_D+1: J10.A6, J10.B6, U14.1
USB_2_D+2: J22.A6, J22.B6, U21.1
USB_2_D+3: J30.A6, J30.B6, U28.1
USB_2_D-: J2.A7, J2.B7, U4.2
USB_2_D-1: J10.A7, J10.B7, U14.2
USB_2_D-2: J22.A7, J22.B7, U21.2
USB_2_D-3: J30.A7, J30.B7, U28.2
USB_D+: J1.A6, J1.B6, U2.5
USB_D+1: J4.A6, J4.B6, U13.5
USB_D+2: J15.A6, J15.B6, U20.5
USB_D+3: J25.A6, J25.B6, U27.5
USB_D-: J1.A7, J1.B7, U2.6
USB_D-1: J4.A7, J4.B7, U13.6
USB_D-2: J15.A7, J15.B7, U20.6
USB_D-3: J25.A7, J25.B7, U27.6
VCCIO: C22.1, C23.1, DSR_DIR.3, IC1.1, IC1.7, IC1.16, IC2.2, IC2.7, IC2.16, J5.5, JP2.3, Q5.1, R29.2, R31.1, R42.1, U7.P2
VCCIO1: C45.1, C46.1, DSR_DIR1.3, IC3.1, IC3.7, IC3.16, IC4.2, IC4.7, IC4.16, J12.5, JP5.3, Q11.1, R54.2, R56.1, R66.1, U11.P2
VCCIO2: C70.1, C71.1, DSR_DIR2.3, IC5.1, IC5.7, IC5.16, IC6.2, IC6.7, IC6.16, J24.5, JP8.3, Q19.1, R93.2, R95.1, R105.1, U18.P2
VCCIO3: C95.1, C96.1, DSR_DIR3.3, IC7.1, IC7.7, IC7.16, IC8.2, IC8.7, IC8.16, J32.5, JP11.3, Q27.1, R132.2, R134.1, R144.1, U25.P2
VIN: C1.1, C13.1, C26.1, D1.C, D3.C, D5.C, D6.C, DVEXT.2, R5.2, U3.1, U5.8, VIN_LED.2
VIN1: C2.1, C27.1, C50.1, D23.C, D24.C, D25.C, D28.C, DVEXT1.2, R41.2, U6.8, U10.1, VIN_LED1.2
VIN2: C51.1, C52.1, C75.1, D37.C, D38.C, D39.C, D42.C, DVEXT2.2, R83.2, U15.8, U17.1, VIN_LED2.2
VIN3: C76.1, C77.1, C100.1, D51.C, D52.C, D53.C, D56.C, DVEXT3.2, R122.2, U22.8, U24.1, VIN_LED3.2
VREG_3.3V: C3.1, C4.1, C5.1, MEAS.1, MEAS.3, U5.1
VREG_3.3V1: C28.1, C29.1, C30.1, MEAS1.1, MEAS1.3, U6.1
VREG_3.3V2: C53.1, C54.1, C55.1, MEAS2.1, MEAS2.3, U15.1
VREG_3.3V3: C78.1, C79.1, C80.1, MEAS3.1, MEAS3.3, U22.1
VSIM: C11.2, C12.2, D8.3, J17.C1, U1.41
VSIM1: C35.2, C36.2, D17.3, J7.C1, U9.41
VSIM2: C60.2, C61.2, D31.3, J18.C1, U16.41
VSIM3: C85.2, C86.2, D45.3, J27.C1, U23.41
V_EXT: F4.2, J5.7
V_EXT1: F8.2, J12.7
V_EXT2: F12.2, J24.7
V_EXT3: F16.2, J32.7

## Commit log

2021-03-04 Updates after concept review
2021-03-09 Update SparkFun_SARA-R5_Breakout.brd
    Added L1 label to GNSS connector
2021-03-10 Proto changes
    Changed the version to v01
    Changed led color of D7 from yellow to green
    Switched text to vector
2021-03-10 Updated file names
2021-05-17 V10
    Added 100k Pulldown resistors to RTS and DTR
    Moved "L1" label from the top of the board to the bottom
2021-05-18 V10 design review changes
    -Updated Schematic PDF
    -Added new parts to sparkfun libraries
    -Fixed labels for schematic sections
2021-05-19 Added V10 Panel
2021-07-08 Update README.md
    Updating readme for product release.
